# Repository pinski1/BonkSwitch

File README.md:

# BonkSwitch
For the remote control of 2 solenoids.

<!-- 3D image of the board here -->

## Specification

* Will accept +30V (8s) to +52 (12s) input voltages on an XT60 connector
* Will drive 2 solenoids with +24V at 60W each via XT30 connectors.
* Has an on board [FrSky XM](https://www.frsky-rc.com/product/xm-1g-sbus-non-telemetry/) reciever with 15 channels
* Will accept any [Adafruit Feather](https://learn.adafruit.com/adafruit-feather/feather-specification) compatible microcontroller board.
* Has voltage monitoring of all power rails and current monitoring of solenoids

While example code is provided it will require modification for your application & chosen Feather.

## Current status

Currently the PCB is in the final stages of review and should be finalised shortly.

The firmware efforts are still on going, although the majority of the work can only be completed once the hardware is available.

## Acknowledgements

* The team behind the robot [Nelly the Ellybot](https://www.facebook.com/teampunchant/)
* The team at [Bristol Bots](https://bristolbotbuilders.com/)
* My friend [Steve](https://twitter.com/BookSwapSteve) for the Feather outline

## Licence
Don't be a tit.
But see LICENCE for more details/legalese.

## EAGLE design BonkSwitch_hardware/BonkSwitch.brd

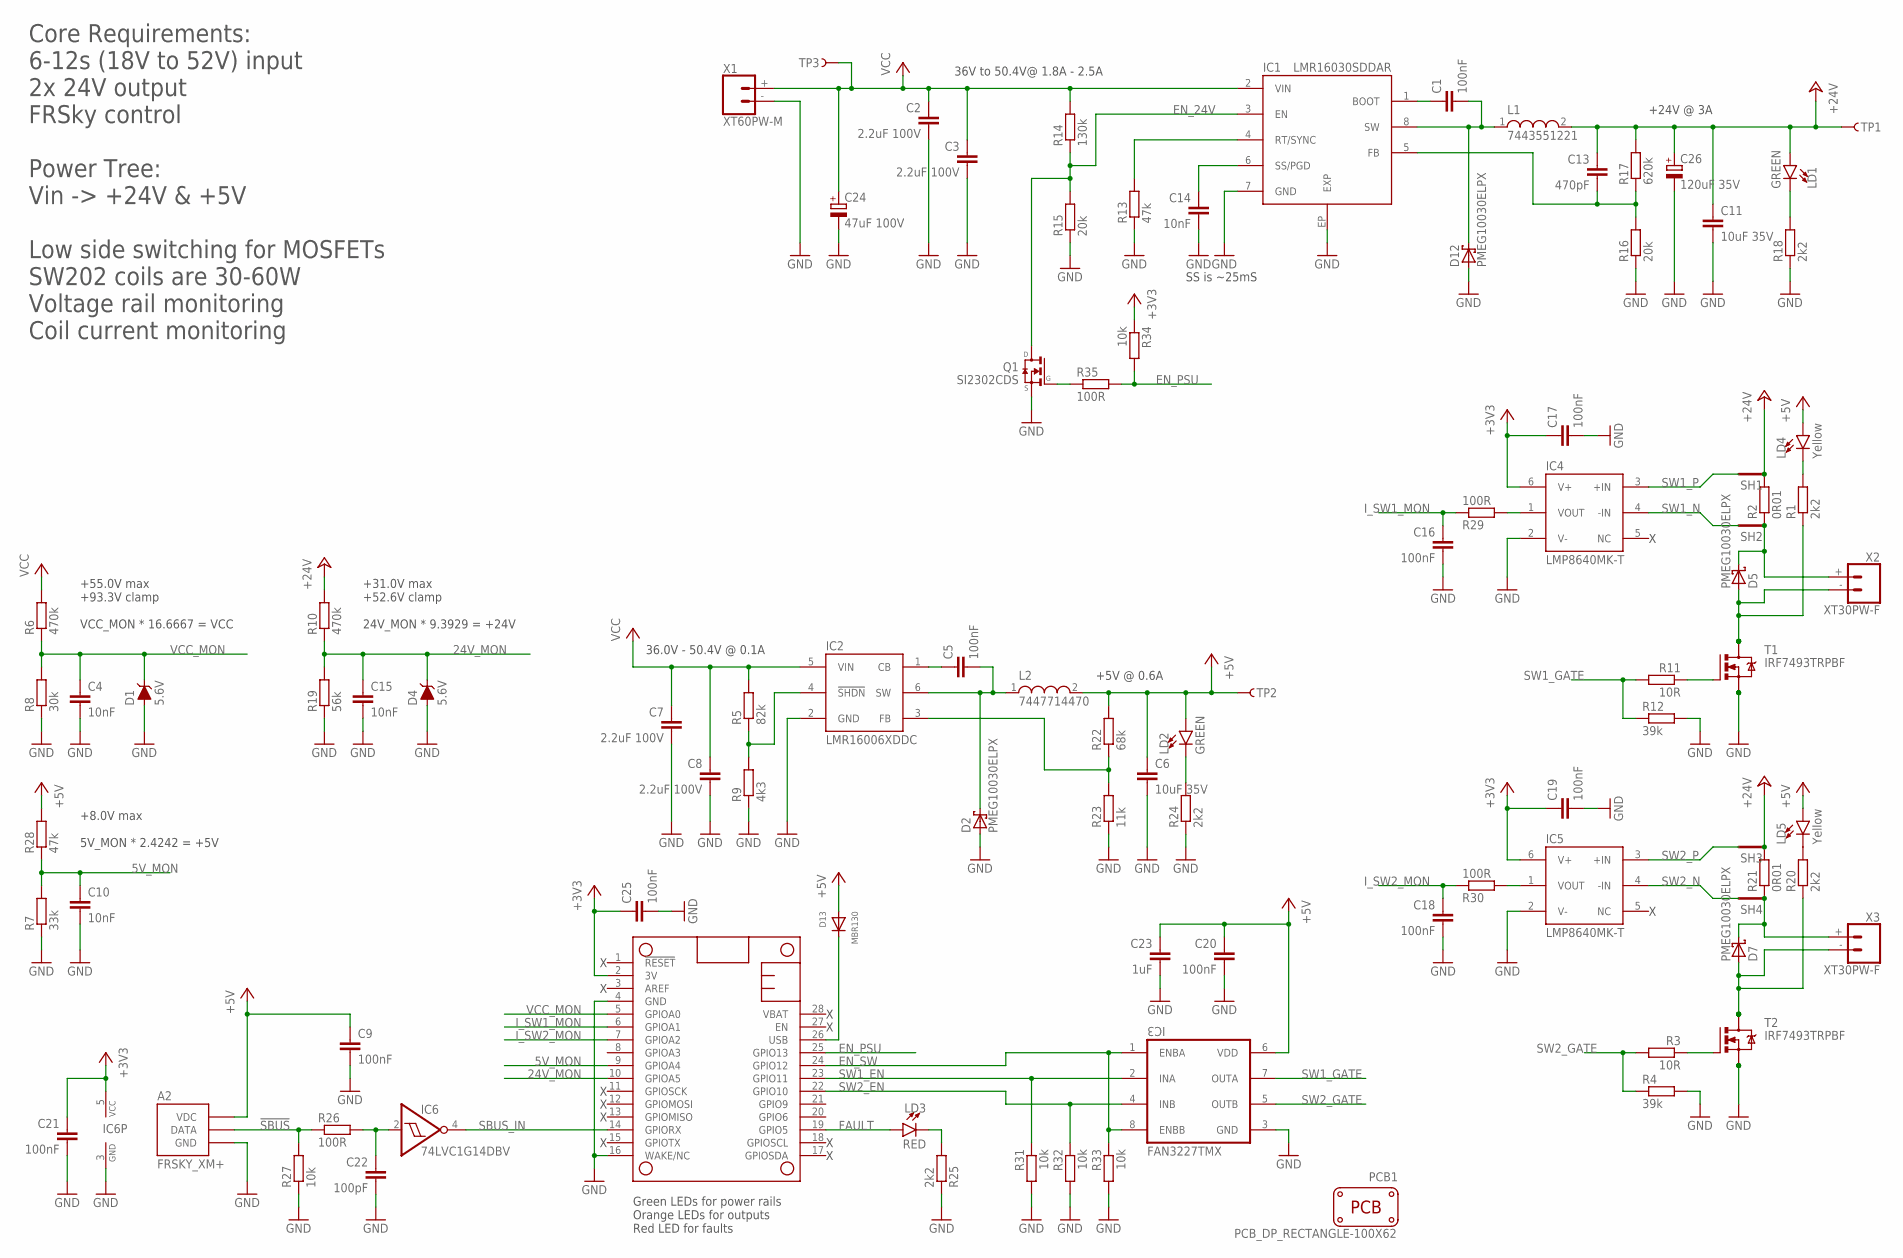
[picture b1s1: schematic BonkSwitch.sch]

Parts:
A1: FEATHERWING_NODIM; FEATHERWING_DIM
A2: FRSKY_XM+
C1, C5, C9, C16, C17, C18, C19, C20, C21, C25: 100nF; C0603
C2, C3, C7, C8: 2.2uF 100V; C1210; MPN C3225X7R2A225K230AB
C4, C10, C14, C15: 10nF; C0603
C6, C11: 10uF 35V; C1210; MPN GMK325AB7106MM-T
C13: 470pF; C0603
C22: 100pF; C0603
C23: 1uF; C0805
C24: 47uF 100V; UD-10X10_NICHICON; MPN EEEHA2A470UP
C26: 120uF 35V; PANASONIC_E; MPN 35SVPF120M
D1, D4: 5.6V; SOD-323; MPN MM3Z4V3ST1G
D2, D5, D7, D12: PMEG10030ELPX; SOD128; MPN PMEG10030ELPX
D13: MBR130; SOD-123; MPN MBR130LSFT1G
IC1: LMR16030SDDAR; HSOIC8; MPN LMR16030SDDA .
IC2: LMR16006XDDC; SOT23-6; MPN LMR16006XDDCR
IC3: FAN3227TMX; SOIC127P600X175-8N; MPN FAN3227TMX
IC4, IC5: LMP8640MK-T; SOT23-6; MPN LMP8640MK-T/NOPB
IC6: 74LVC1G14DBV; SOT23-5; MPN 74LVC1G14GW,125
L1: 7443551221; WE-HCI_1350/1365; MPN 7443551221
L2: 7447714470; WE-PD_1030/1050; MPN 7447714470
LD1, LD2: GREEN; LED-0603
LD3: RED; LED-0603
LD4, LD5: Yellow; LED-0603
PCB1: PCB_DP_RECTANGLE-100X62; DP10062_V1
Q1: SI2302CDS; SOT23; MPN SI2302CDS-T1-GE3
R1, R20, R24, R25: 2k2; R0603
R2, R21: 0R01; R2512; MPN CRA2512-FZ-R010ELF
R3, R11: 10R; R0805
R4, R12: 39k; R0805
R5: 82k; R0603
R6, R10: 470k; R0603
R7: 33k; R0603
R8: 30k; R0603
R9: 4k3; R0603
R13, R28: 47k; R0603
R14: 130k; R0603
R15, R16: 20k; R0603
R17: 620k; R0603
R18: 2k2; R0805
R19: 56k; R0603
R22: 68k; R0603
R23: 11k; R0603
R26, R29, R30, R35: 100R; R0603
R27, R31, R32, R33, R34: 10k; R0603
SH1, SH2, SH3, SH4: SHORTT1; SHORT_TOP-01
T1, T2: IRF7493TRPBF; SO-08; MPN IRF7493TRPBF
TP1, TP2, TP3: TESTPOINT_1.5X1.5; TESTPAD_1.5X1.5
X1: XT60PW-M
X2, X3: XT30PW-F

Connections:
5V_MON: A1.9 (GPIOA4), C10.1, R7.2, R28.1
24V_MON: A1.10 (GPIOA5), C15.1, D4.C, R10.1, R19.2
!SBUS: A2.3 (DATA), R26.1, R27.2
!SBUS_FILT: C22.1, IC6.2 (I), R26.2
+3V3: A1.2 (3V), C17.1, C19.1, C21.1, C25.1, IC4.6 (V+), IC5.6 (V+), IC6.5 (VCC), R34.1
+5V: A2.2 (VDC), C6.1, C9.1, C20.1, C23.1, D13.A, IC3.6 (VDD), L2.2, LD2.A, LD4.A, LD5.A, R22.2, R28.2, TP2.1
+24V: C11.1, C13.1, C26.+, L1.2, LD1.A, R2.2, R10.2, R17.2, R21.2, SH1.1, SH3.1, TP1.1
BST_5V: C5.1, IC2.1 (CB)
BST_24V: C1.1, IC1.1 (BOOT)
EN_5V: IC2.4 (!SHDN!), R5.1, R9.2
EN_24V: IC1.3 (EN), Q1.3 (D), R14.1, R15.2
EN_PSU: A1.25 (GPIO13), R34.2, R35.2
EN_SW: A1.24 (GPIO12), IC3.1 (ENBA), IC3.8 (ENBB), R33.1
FAULT: A1.19 (GPIO5), LD3.A
FB_5V: IC2.3 (FB), R22.1, R23.2
FB_24V: C13.2, IC1.5 (FB), R16.2, R17.1
GND: A1.4 (GND), A1.16 (WAKE/NC), A2.1 (GND), C2.2, C3.2, C4.2, C6.2, C7.2, C8.2, C9.2, C10.2, C11.2, C14.2, C15.2, C16.2, C17.2, C18.2, C19.2, C20.2, C21.2, C22.2, C23.2, C24.-, C25.2, C26.-, D1.A, D2.A, D4.A, D12.A, IC1.7 (GND), IC1.EP (EXP), IC2.2 (GND), IC3.3 (GND), IC4.2 (V-), IC5.2 (V-), IC6.3 (GND), Q1.2 (S), R4.2, R7.1, R8.1, R9.1, R12.2, R13.1, R15.1, R16.1, R18.1, R19.1, R23.1, R24.1, R25.1, R27.1, R31.2, R32.2, R33.2, T1.1 (S), T1.2 (S), T1.3 (S), T2.1 (S), T2.2 (S), T2.3 (S), X1.- (1)
I_SW1: IC4.1 (VOUT), R29.2
I_SW1_MON: A1.6 (GPIOA1), C16.1, R29.1
I_SW2: IC5.1 (VOUT), R30.2
I_SW2_MON: A1.7 (GPIOA2), C18.1, R30.1
unnamed: D7.C, R21.1, SH4.1, X3.+ (2)
unnamed: Q1.1 (G), R35.1
unnamed: R11.1, T1.4 (G)
unnamed: D5.A, R1.1, T1.5 (D), T1.6 (D), T1.7 (D), T1.8 (D), X2.- (1)
unnamed: LD4.C, R1.2
unnamed: R3.1, T2.4 (G)
unnamed: D7.A, R20.1, T2.5 (D), T2.6 (D), T2.7 (D), T2.8 (D), X3.- (1)
unnamed: LD5.C, R20.2
unnamed: D5.C, R2.1, SH2.1, X2.+ (2)
unnamed: LD3.C, R25.2
unnamed: LD1.C, R18.2
unnamed: LD2.C, R24.2
RT_24V: IC1.4 (RT/SYNC), R13.2
SBUS_IN: A1.14 (GPIORX), IC6.4 (O)
SS_24V: C14.1, IC1.6 (SS/PGD)
SW1_EN: A1.23 (GPIO11), IC3.2 (INA), R31.1
SW1_GATE: IC3.7 (OUTA), R11.2, R12.1
SW1_N: IC4.4 (-IN), SH2.2
SW1_P: IC4.3 (+IN), SH1.2
SW2_EN: A1.22 (GPIO10), IC3.4 (INB), R32.1
SW2_GATE: IC3.5 (OUTB), R3.2, R4.1
SW2_N: IC5.4 (-IN), SH4.2
SW2_P: IC5.3 (+IN), SH3.2
SW_5V: C5.2, D2.C, IC2.6 (SW), L2.1
SW_24V: C1.2, D12.C, IC1.8 (SW), L1.1
VCC: C2.1, C3.1, C7.1, C8.1, C24.+, IC1.2 (VIN), IC2.5 (VIN), R5.2, R6.2, R14.2, TP3.1, X1.+ (2)
VCC_MON: A1.5 (GPIOA0), C4.1, D1.C, R6.1, R8.2
V_USB: A1.26 (USB), D13.C

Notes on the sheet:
Core Requirements: 6-12s (18V to 52V) input 2x 24V output FRSky control Power Tree: Vin -> +24V & +5V Low side switching for MOSFETs SW202 coils are 30-60W Voltage rail monitoring Coil current monitoring
+55.0V max +93.3V clamp VCC_MON * 16.6667 = VCC
+31.0V max +52.6V clamp 24V_MON * 9.3929 = +24V
+24V @ 3A
36V to 50.4V@ 1.8A - 2.5A
+5V @ 0.6A
36.0V - 50.4V @ 0.1A
Green LEDs for power rails Orange LEDs for outputs Red LED for faults
SS is ~25mS
+8.0V max 5V_MON * 2.4242 = +5V

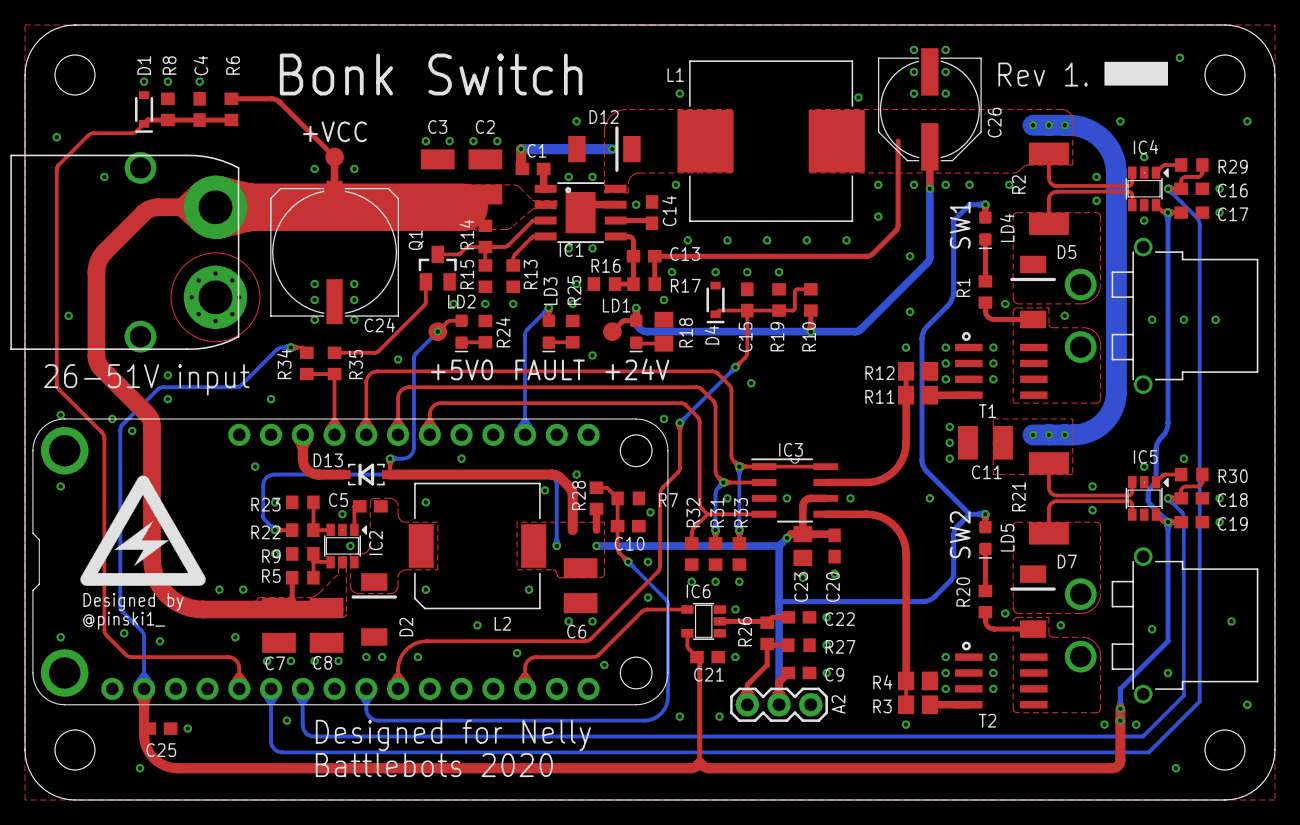
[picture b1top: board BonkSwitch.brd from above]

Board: 2 copper layers, 100.0 x 62.0 mm, 97 parts (0 on the bottom side), 49 nets.

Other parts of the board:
LG1: LOGO_10X10

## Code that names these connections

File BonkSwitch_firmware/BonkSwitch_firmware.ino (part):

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#define PIN_VCC_MON       (A0)
#define PIN_24V_MON       (A5)
#define PIN_5V_MON        (A4)
#define PIN_I_SW1_MON     (A1)
#define PIN_I_SW2_MON     (A2)
#define PIN_EN_PSU        (13)  // active low
#define PIN_EN_SW         (12)
#define PIN_SW1_EN        (11)
#define PIN_SW2_EN        (10)
#define PIN_FAULT         (5)
#define PIN_SBUS_IN       (0)

/** Prototypes **/
unsigned int convert_ADC(int channel);
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  pinMode(PIN_VCC_MON, INPUT);
  pinMode(PIN_24V_MON, INPUT);
  pinMode(PIN_5V_MON, INPUT);
  pinMode(PIN_I_SW1_MON, INPUT);
  pinMode(PIN_I_SW2_MON, INPUT);
  pinMode(PIN_EN_PSU, OUTPUT);
  pinMode(PIN_EN_SW, OUTPUT);
  pinMode(PIN_SW1_EN, OUTPUT);
  pinMode(PIN_SW2_EN, OUTPUT);
  pinMode(PIN_FAULT, OUTPUT);

  digitalWrite(PIN_EN_PSU, HIGH);
  digitalWrite(PIN_EN_SW, HIGH);
  digitalWrite(PIN_SW1_EN, LOW);
  digitalWrite(PIN_SW2_EN, LOW);
  digitalWrite(PIN_FAULT, HIGH);

  for (int i = 0; i < 20; i++)
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    eqv_12v = ((12000 * 256) / mon_24v);

    // get latest coil currents
    mon_sw1 = convert_ADC(PIN_I_SW1_MON);
    coil_current[0][coil_curr_index] = mon_sw1;
    mon_sw2 = convert_ADC(PIN_I_SW2_MON);
    coil_current[1][coil_curr_index] = mon_sw2;
    if (coil_curr_index == 19) coil_curr_index = 0;
    else coil_curr_index += 1;
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        }
        // SBUS status?
        //Serial.print(""); 
        Serial.print("The +24V PSU is "); Serial.println(!digitalRead(PIN_EN_PSU) ? "enabled" : "disabled");
        Serial.print("The switches are "); Serial.println(digitalRead(PIN_EN_SW) ? "enabled" : "disabled");
        Serial.print("Switch 1 is "); Serial.println(digitalRead(PIN_SW1_EN) ? "enabled" : "disabled");
        Serial.print("Switch 2 is "); Serial.println(digitalRead(PIN_SW2_EN) ? "enabled" : "disabled");
        Serial.print("There is "); Serial.println(digitalRead(PIN_FAULT) ? "a fault!" : "not a fault");
      }
      else if (debug_buffer.substring(0, debug_buffer.indexOf('\r')) == "PSU EN")
      {
        Serial.println("Enabling +24V PSU");
        digitalWrite(PIN_EN_PSU, LOW);
      }
      else if (debug_buffer.substring(0, debug_buffer.indexOf('\r')) == "PSU DIS")
      {
        Serial.println("Disabling +24V PSU");
        digitalWrite(PIN_EN_PSU, HIGH);
      }
      else if (debug_buffer.substring(0, debug_buffer.indexOf('\r')) == "SW1 EN")
      {
        Serial.println("Enabling SW1");
        digitalWrite(PIN_SW1_EN, HIGH);
      }
      else if (debug_buffer.substring(0, debug_buffer.indexOf('\r')) == "SW1 DIS")
      {
        Serial.println("Disabling SW1");
        digitalWrite(PIN_SW1_EN, LOW);
      }
      else if (debug_buffer.substring(0, debug_buffer.indexOf('\r')) == "SW2 EN")
      {
        Serial.println("Enabling SW2");
        digitalWrite(PIN_SW2_EN, HIGH);
      }
      else if (debug_buffer.substring(0, debug_buffer.indexOf('\r')) == "SW2 DIS")
      {
        Serial.println("Disabling SW2");
        digitalWrite(PIN_SW2_EN, LOW);
      }
      debug_buffer.remove(0);
    }
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    switch (current_state)
    {
      case s_Idle:
        digitalWrite(PIN_EN_PSU, LOW);
        digitalWrite(PIN_FAULT, LOW);
        digitalWrite(PIN_SW1_EN, LOW); analogWrite(PIN_SW1_EN, 0);
        digitalWrite(PIN_SW2_EN, LOW); analogWrite(PIN_SW2_EN, 0);
        
        if(counter_packet_missed > 5 || channels[0] < 100) current_state = s_Failsafe;
        else if (channels[0] > 1500)  current_state = s_Firing;
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        break;
      case s_Firing:
        // enable firing solenoid
        digitalWrite(PIN_SW1_EN, HIGH);
        
        // ensure it doesn't over heat
        delay(3);
        analogWrite(PIN_SW1_EN, eqv_12v);
        
        if(counter_packet_missed > 5 || channels[0] < 100) current_state = s_Failsafe;
        else if (channels[0] > 700 && channels[0] < 1500)  current_state = s_Idle;
        break;
      case s_Returning:
        // enable retract solenoid
        digitalWrite(PIN_SW2_EN, HIGH);
        
        // ensure it doesn't over heat
        delay(3);
        analogWrite(PIN_SW2_EN, eqv_12v);
        
        if(counter_packet_missed > 5 || channels[0] < 100) current_state = s_Failsafe;
        else if (channels[0] > 700 && channels[0] < 1500)  current_state = s_Idle;
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      case s_Failsafe:
      default:
        digitalWrite(PIN_FAULT, HIGH);
        digitalWrite(PIN_EN_PSU, HIGH);
        digitalWrite(PIN_SW1_EN, LOW);
        digitalWrite(PIN_SW2_EN, LOW);
        
        // monitor inputs for problems

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    case PIN_5V_MON:
      adc_value *= _conv_5v;
      break;
    case PIN_I_SW1_MON:
    case PIN_I_SW2_MON:
      adc_value *= _conv_i_sw;
      break;
    default:
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
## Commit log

2020-04-25 Initial commit
    Firmware is not complete.
2020-04-25 Reorganising HW.
2020-04-25 More directory reorg
2020-04-25 Tuning Schematic.
2020-04-25 Fixed SBUS bias resistor.
2020-04-25 Firmware a bit more fleshed out
2020-04-25 Moved +5V rail monitoring to A4
2020-04-26 Updated schematic & BoM
2020-04-27 Adding Zener part numbers
2020-06-26 Adding switch control and SBUS decoding.
2021-09-02 Adding TI Current Controlled Driver for Solenoids app note

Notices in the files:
parts and their libraries:
SparkFun-DiscreteSemi: Licensing: Creative Commons ShareAlike 4.0 International - https://creativecommons.org/licenses/by-sa/4.0
WE-PD2: Copyright: Würth Elektronik
